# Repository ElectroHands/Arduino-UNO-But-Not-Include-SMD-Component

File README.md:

# Arduino-UNO-But-Not-Include-SMD-Component

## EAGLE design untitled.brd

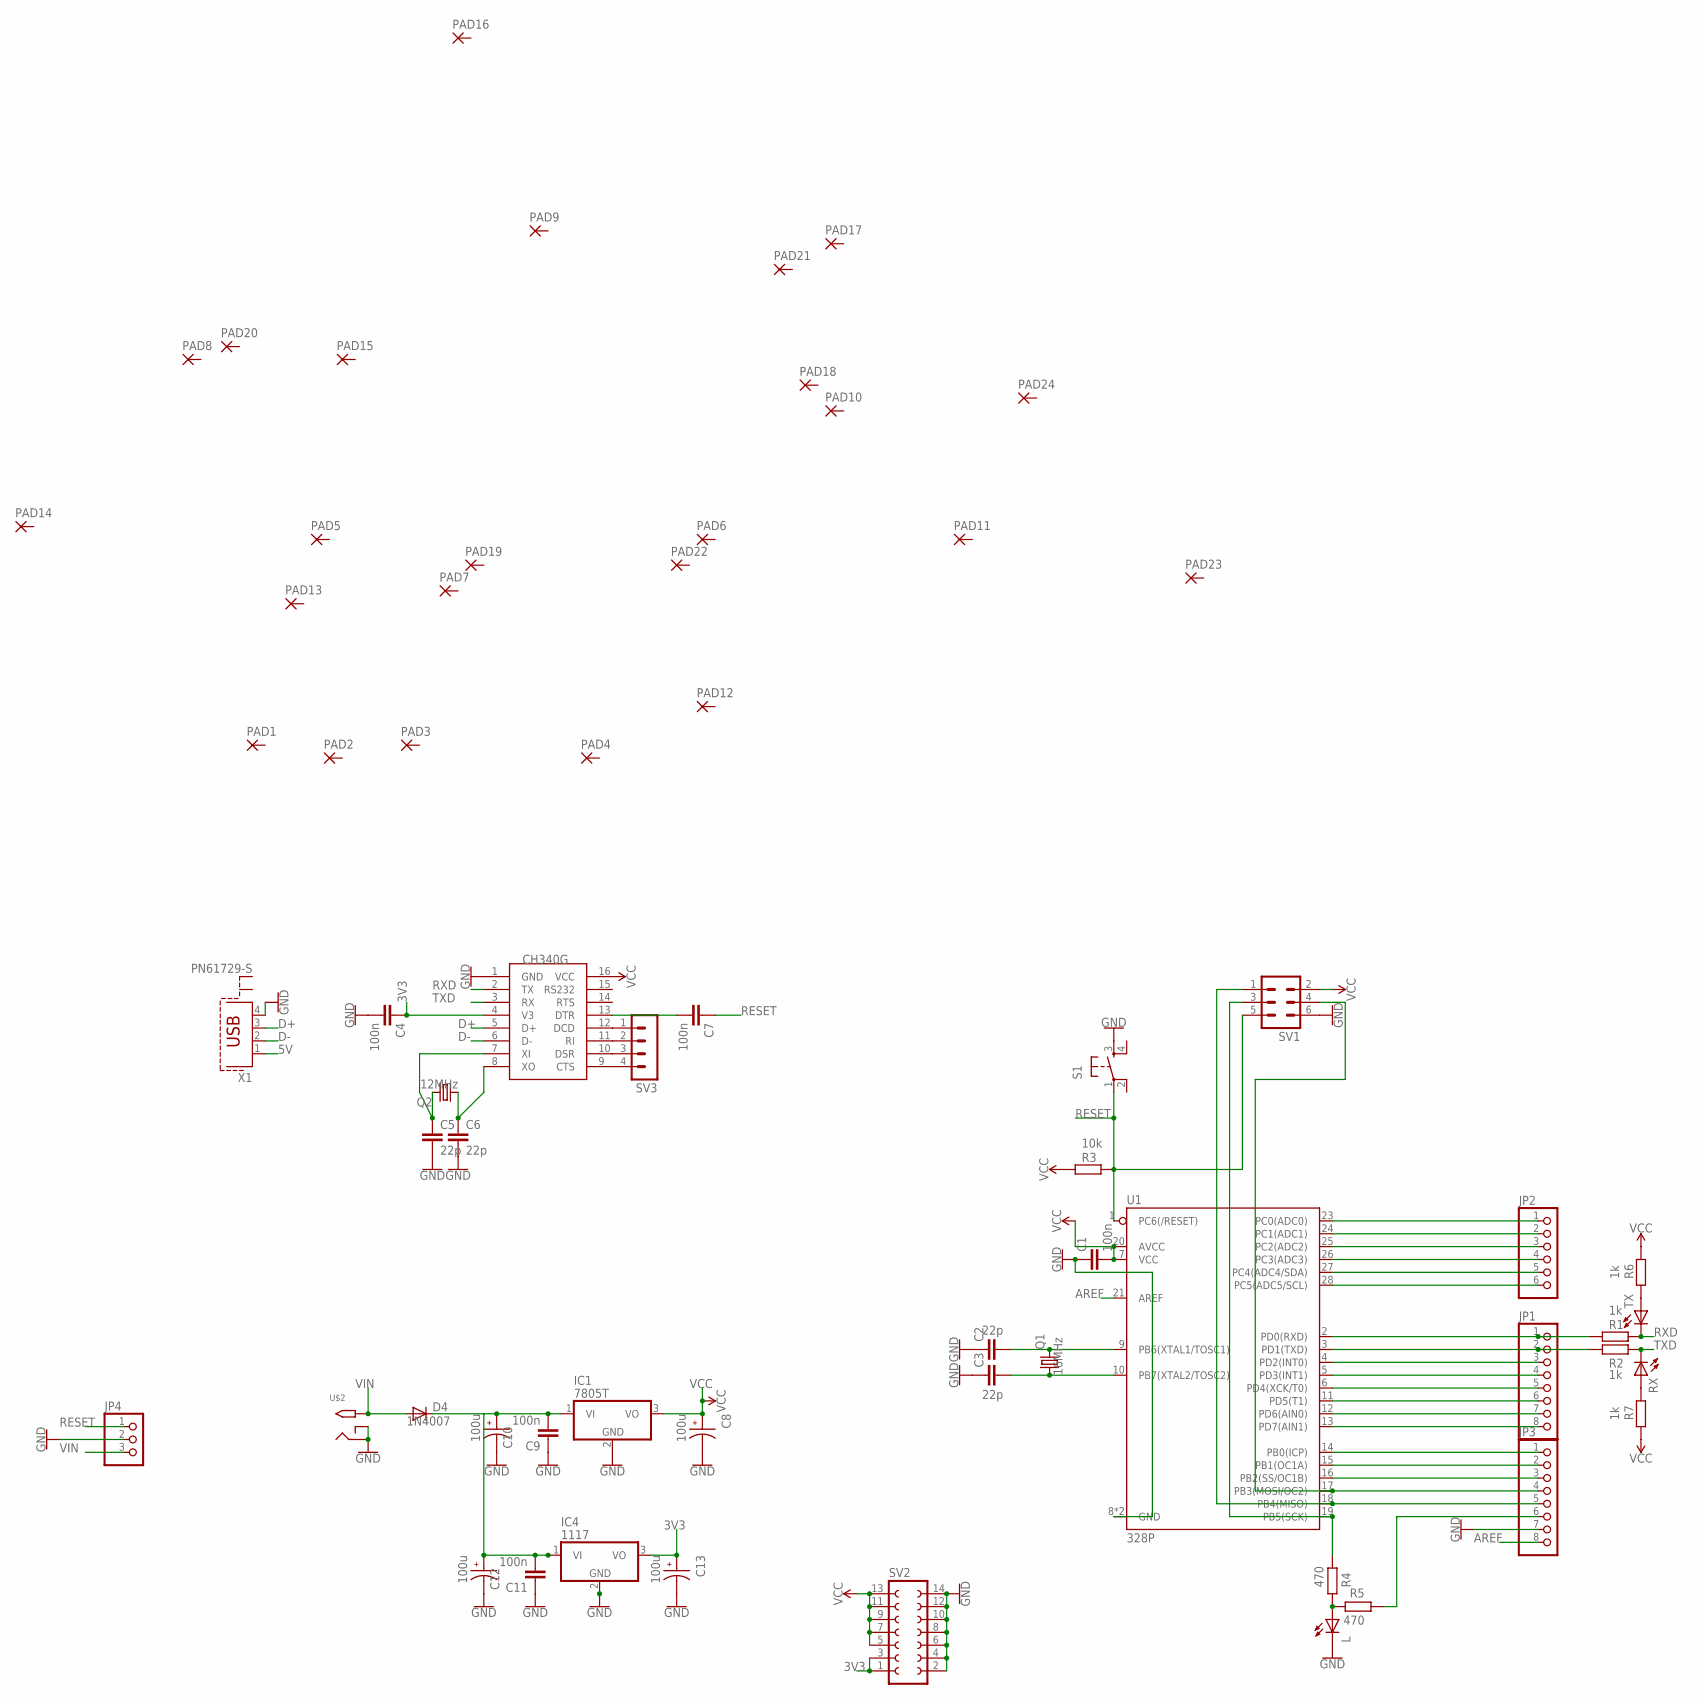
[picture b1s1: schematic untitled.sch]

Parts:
C1, C4, C7, C9, C11: 100n; C2.5-3
C2, C3, C5, C6: 22p; C2.5-3
C8, C10, C12, C13: 100u; CAPPRD500W50D500H1100
D4: 1N4007; DO41-10
IC1: 7805T; TO220H
IC4: 1117; TO220H
JP1, JP3: PINHD-1X8CLEANBIG; 1X08-CLEANBIG
JP2: PINHD-1X6; 1X06
JP4: PINHD-1X3; 1X03
L: LED3MM
PAD1, PAD2, PAD3, PAD4, PAD5, PAD6, PAD7, PAD8, PAD9, PAD10, PAD11, PAD12, PAD13, PAD14, PAD15, PAD16, PAD17, PAD18, PAD19, PAD20, PAD21, PAD22, PAD23, PAD24: SMD5; SMD2,54-5,08
Q1: 16MHz; HC49/S
Q2: 12MHz; HC49/S
R1, R2, R6, R7: 1k; 0204/7
R3: 10k; 0204/7
R4, R5: 470; 0204/7
RX: LED3MM
S1: TAC_SWITCHPTH; TACTILE-PTH
SV1: MA03-2
SV2: FE07-2
SV3: MA04-1
TX: LED3MM
U1: 328P; DIP28
U$1: CH340G; SOIC16
U$2: 2.1MMJACKTHM; PJ-102A
X1: PN61729-S

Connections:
3V3: C4.1, C13.P, IC4.3 (VO), SV2.1, SV2.3, U$1.4 (V3)
5V: X1.1
AREF: JP3.8, U1.21 (AREF)
D+: U$1.5 (D+), X1.3
D-: U$1.6 (D-), X1.2
GND: C1.1, C2.1, C3.1, C4.2, C5.2, C6.2, C8.N, C9.1, C10.N, C11.1, C12.N, C13.N, IC1.2 (GND), IC4.2 (GND), JP3.7, JP4.2, L.K (C), S1.3, SV1.6, SV2.2, SV2.4, SV2.6, SV2.8, SV2.10, SV2.12, SV2.14, U1.8 (GND), U1.22 (GND), U$1.1 (GND), U$2.RING, U$2.RING_SW, X1.4
unnamed: JP1.1, R1.1, U1.2 (PD0(RXD))
unnamed: JP1.2, R2.1, U1.3 (PD1(TXD))
unnamed: JP1.3, U1.4 (PD2(INT0))
unnamed: JP1.4, U1.5 (PD3(INT1))
unnamed: JP1.5, U1.6 (PD4(XCK/T0))
unnamed: JP1.6, U1.11 (PD5(T1))
unnamed: JP1.7, U1.12 (PD6(AIN0))
unnamed: JP1.8, U1.13 (PD7(AIN1))
unnamed: JP2.1, U1.23 (PC0(ADC0))
unnamed: JP2.2, U1.24 (PC1(ADC1))
unnamed: JP2.3, U1.25 (PC2(ADC2))
unnamed: JP2.4, U1.26 (PC3(ADC3))
unnamed: JP2.5, U1.27 (PC4(ADC4/SDA))
unnamed: JP2.6, U1.28 (PC5(ADC5/SCL))
unnamed: JP3.1, U1.14 (PB0(ICP))
unnamed: JP3.2, U1.15 (PB1(OC1A))
unnamed: JP3.3, U1.16 (PB2(SS/OC1B))
unnamed: JP3.4, SV1.4, U1.17 (PB3(MOSI/OC2))
unnamed: JP3.5, SV1.1, U1.18 (PB4(MISO))
unnamed: R4.2, SV1.3, U1.19 (PB5(SCK))
unnamed: C2.2, Q1.2, U1.9 (PB6(XTAL1/TOSC1))
unnamed: C3.2, Q1.1, U1.10 (PB7(XTAL2/TOSC2))
unnamed: SV3.1, U$1.12 (DCD)
unnamed: JP3.6, R5.1
unnamed: C5.1, Q2.2, U$1.7 (XI)
unnamed: C6.1, Q2.1, U$1.8 (XO)
unnamed: L.A, R4.1, R5.2
unnamed: SV3.2, U$1.11 (RI)
unnamed: SV3.3, U$1.10 (DSR)
unnamed: SV3.4, U$1.9 (CTS)
unnamed: C7.2, U$1.13 (DTR)
unnamed: R6.1, TX.A
unnamed: C9.2, C10.P, C11.2, C12.P, D4.C, IC1.1 (VI), IC4.1 (VI)
unnamed: R7.2, RX.A
RESET: C7.1, JP4.1, R3.2, S1.1, SV1.5, U1.1 (PC6(/RESET))
RXD: R1.2, TX.K (C), U$1.2 (TX)
TXD: R2.2, RX.K (C), U$1.3 (RX)
VCC: C1.2, C8.P, IC1.3 (VO), R3.1, R6.2, R7.1, SV1.2, SV2.5, SV2.7, SV2.9, SV2.11, SV2.13, U1.7 (VCC), U1.20 (AVCC), U$1.16 (VCC)
VIN: D4.A, JP4.3, U$2.TIP

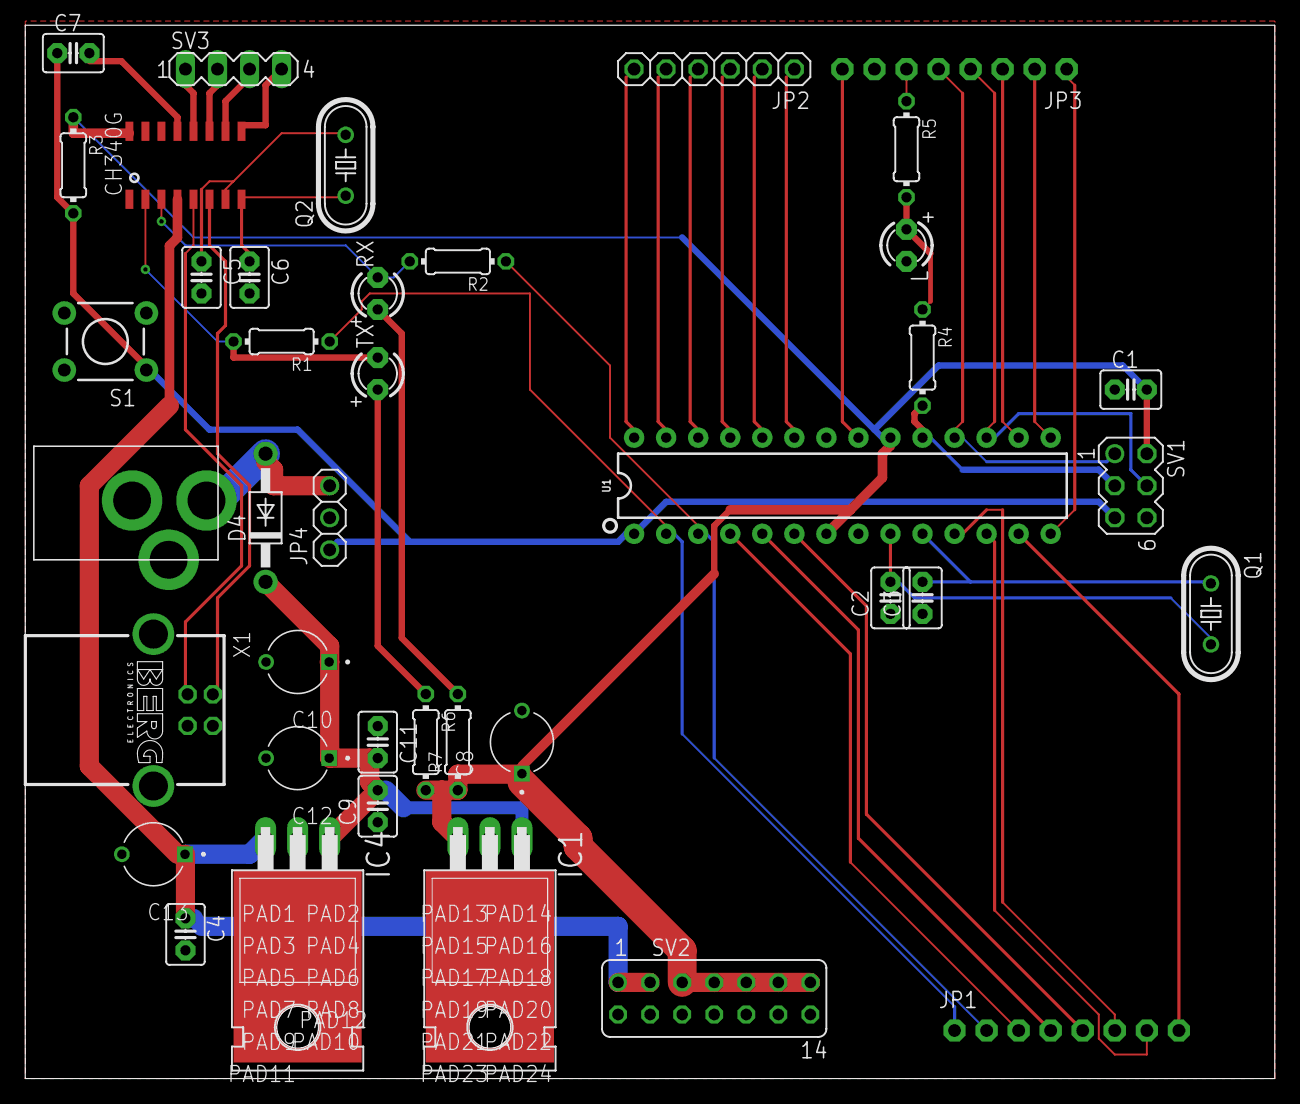
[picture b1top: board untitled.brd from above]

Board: 2 copper layers, 99.0 x 83.5 mm, 64 parts (0 on the bottom side), 44 nets.

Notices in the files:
parts and their libraries:
SparkFun-Retired: Licensing: Creative Commons ShareAlike 4.0 International - https://creativecommons.org/licenses/by-sa/4.0
